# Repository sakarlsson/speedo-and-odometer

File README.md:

# speedo-and-odometer
Arduino based speedometer and odometer

Made to work for my El Camino 1970 with a Holley Terminator X EFI.

The code is now a bit more generally useful.

The odometer is using a Adafruit Monochrome 128x32 I2C OLED graphic
display [ADA931].  It will store the current km reading in the eeprom
(using a rotating scheme to get more than the 100000 writes per cell).

The speedo is using the SwitechX25 lib.
Beware that this lib has a little flaw when it comes to the zero()
function.  It does not use its acceleration mechanism and steps
may stall.    You may need to tweak this in the SwitechX25.cpp 

```#define RESET_STEP_MICROSEC 800
```

## Usage

### Compile

Use the library manger to fetch the used libs. These are needed:

    #include <Adafruit_GFX.h>
    #include <Adafruit_SSD1306.h>

Compile and load the Arduino with the code using the normal Arduino IDE.

I use: 

	arduino-cli compile -b arduino:avr:nano
	arduino-cli upload -p /dev/ttyUSB0  -b arduino:avr:nano:cpu=atmega328old
	
	arduino-cli monitor  -p /dev/ttyUSB0

### Run

Use the Arduino serial console to configure the speedometer.
You need to issue the following commands:

* `set zeromark value`  To configure the position of the zero speed mark.
* `set maxmark value`   To configure the position of the maximum speed mark
* `set maxspeed value`  To configure what speed it is at the max speed mark

To help you figure out the positions you can use

    moveto position

It will move the dial to the poistion - the position is in terms steps of the Switec motor.
When you have found the position of zero, give `set zero <value>`, and the
position will be saved to the internal eeprom.  Proceed with finding the position for
the max speed mark. 

When you have set the above 3 parameters, you can try it out by simulating
a speed:

    speed 120

## General mounting etc

I used the Arduino Nano for a small form factor and milled out a plastic console
out of POM to hold it all together.

For the tachometer I had to CNC mill a new needle as I couldn't reuse the original.

The speedo will get power from the IGN 12+V, but the tachometer will have constant
battery power. As it will not otherwise be able to go to Zero when you turn off the IGN.

The tachometer code will enter Low Power mode when there are no pulses detected, and
did draw about 2-3 mA (after I desoldered the power LED on the Nano).

The Holley Terminator X was programmed to output the Speed on one of the free output pins.

# draw-gauge.py 

Is a small script that works with the Inkscape Simple Scripting extension 

## Useful links:

https://guy.carpenter.id.au/gaugette/2012/01/19/x12-quad-driver-chip/

### To find the X25 driver search for: 

X12.017 AX1201728 AX1201728SG SOP-28

## X27 motor pins 

The X27 168 has built in stops at 0 and max
Pin out: Poke the needle pin at your nose and orient the text X27 168 so you can read it.
         Then pin 1 is to the top left (protruding out on the the other side)
         pin 2 follows counter clock wise, then 3 and 4 which is to the top right.

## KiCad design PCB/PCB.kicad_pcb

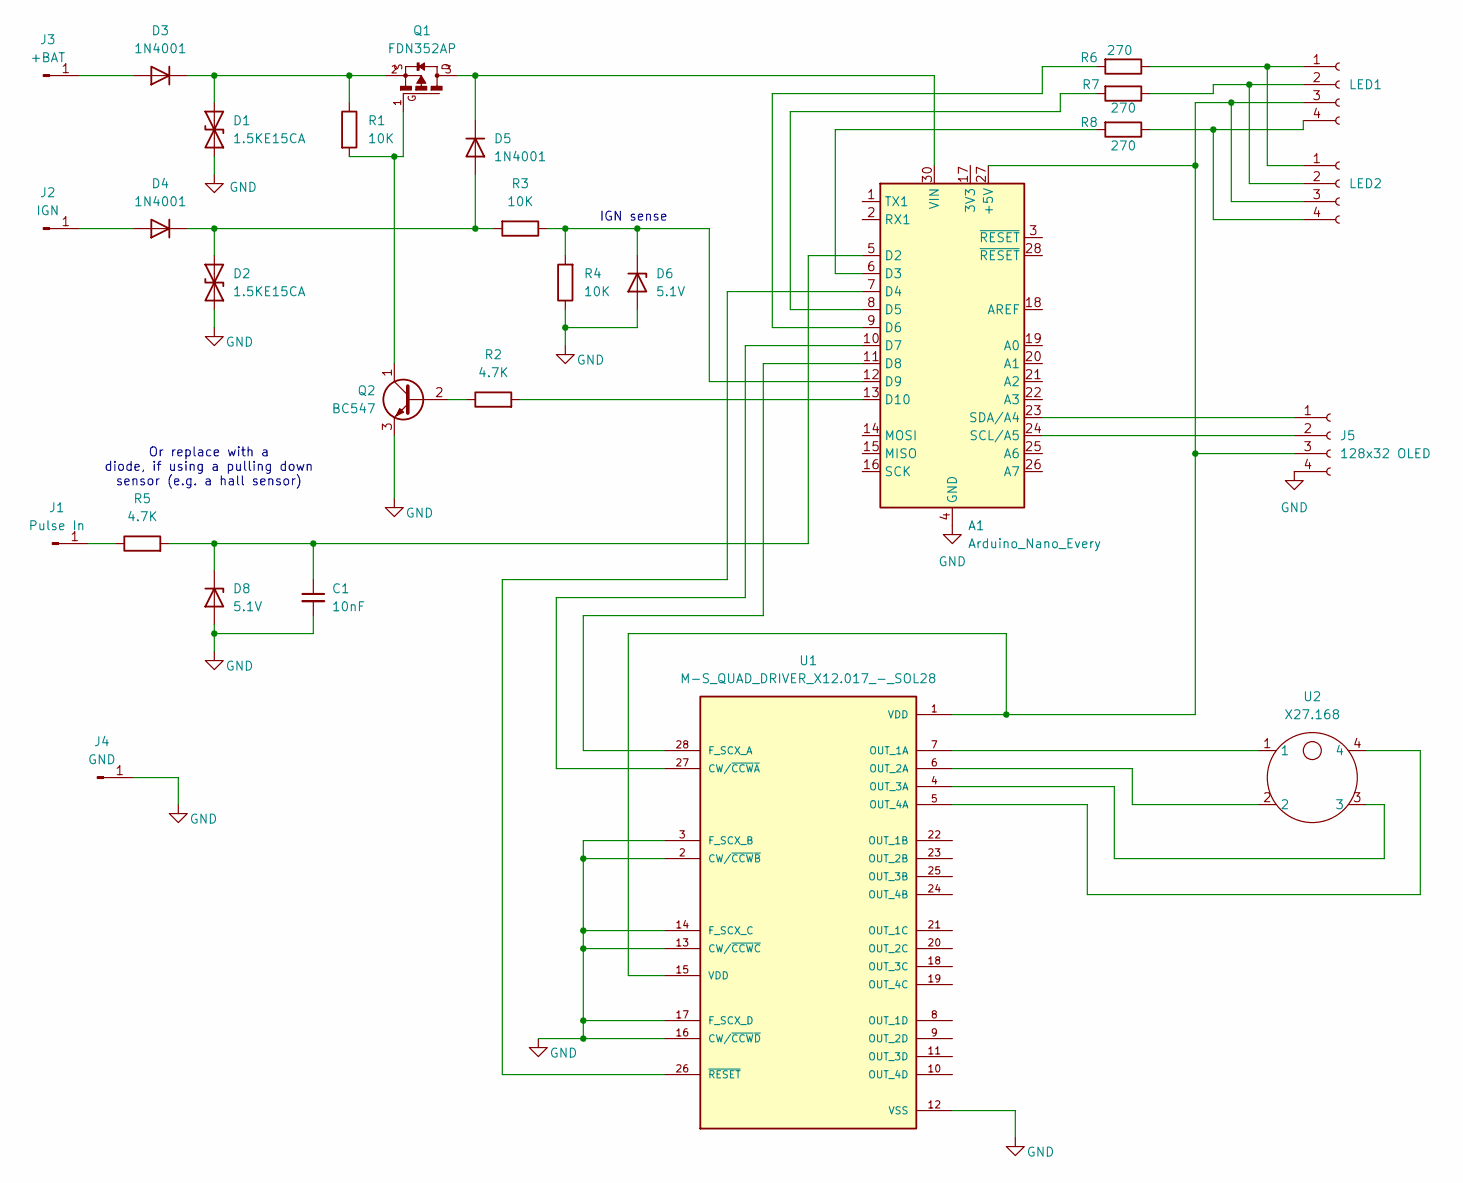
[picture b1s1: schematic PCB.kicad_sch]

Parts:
A1: Arduino_Nano_Every; Arduino_Nano
C1: 10nF; C_Disc_D7.5mm_W4.4mm_P5.00mm
D1, D2: 1.5KE15CA; D_DO-201AE_P5.08mm_Vertical_KathodeUp
D3, D4, D5: 1N4001; D_DO-41_SOD81_P3.81mm_Vertical_KathodeUp
D6, D8: 5.1V; D_DO-35_SOD27_P2.54mm_Vertical_KathodeUp
J1: Pulse In; SolderWire-0.5sqmm_1x01_D0.9mm_OD2.3mm
J2: IGN; SolderWire-0.5sqmm_1x01_D0.9mm_OD2.3mm
J3: +BAT; SolderWire-0.5sqmm_1x01_D0.9mm_OD2.3mm
J4: GND; SolderWire-0.5sqmm_1x01_D0.9mm_OD2.3mm
J5: 128x32 OLED; PinHeader_1x04_P2.54mm_Vertical
LED1: LED1; rgb-led
LED2: LED2; rgb-led
Q1: FDN352AP; SSOT-3
Q2: BC547; TO-92_Inline
R1, R3, R4: 10K; R_Axial_DIN0207_L6.3mm_D2.5mm_P2.54mm_Vertical
R2, R5: 4.7K; R_Axial_DIN0207_L6.3mm_D2.5mm_P2.54mm_Vertical
R6, R7, R8: 270; R_Axial_DIN0207_L6.3mm_D2.5mm_P2.54mm_Vertical
U1: M-S_QUAD_DRIVER_X12.017_-_SOL28; SOIC127P1028X264-28N; PARTREV --
U2: X27.168; x27.168

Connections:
GND: A1.4 (GND), A1.29 (GND), C1.2, D1.1 (A1), D2.1 (A1), D6.2 (A), D8.2 (A), J4.1, J5.4, Q2.3 (E), R4.1, U1.2 (CW/~CCW~B), U1.3 (F_SCX_B), U1.12 (VSS), U1.13 (CW/~CCW~C), U1.14 (F_SCX_C), U1.16 (CW/~CCW~D), U1.17 (F_SCX_D)
unnamed: A1.5 (D2), C1.1, D8.1 (K), R5.2
unnamed: A1.6 (D3), R8.2
unnamed: A1.7 (D4), U1.26 (~RESET)
unnamed: A1.8 (D5), R7.2
unnamed: A1.9 (D6), R6.2
unnamed: A1.10 (D7), U1.27 (CW/~CCW~A)
unnamed: A1.11 (D8), U1.28 (F_SCX_A)
unnamed: A1.12 (D9), D6.1 (K), R3.1, R4.2
unnamed: A1.13 (D10), R2.2
unnamed: A1.24 (SCL/A5), J5.2
unnamed: A1.23 (SDA/A4), J5.1
unnamed: A1.30 (VIN), D5.1 (K), Q1.3
unnamed: D1.2 (A2), D3.1 (K), Q1.2, R1.1
unnamed: D2.2 (A2), D4.1 (K), D5.2 (A), R3.2
unnamed: D3.2 (A), J3.1
unnamed: D4.2 (A), J2.1
unnamed: J1.1, R5.1
unnamed: LED1.1, LED2.1, R6.1
unnamed: LED1.2, LED2.2, R7.1
unnamed: LED1.4, LED2.4, R8.1
unnamed: Q2.2 (B), R2.1
unnamed: Q1.1, Q2.1 (C), R1.2
unnamed: U1.7 (OUT_1A), U2.1
unnamed: U1.6 (OUT_2A), U2.2
unnamed: U1.4 (OUT_3A), U2.3
unnamed: U1.5 (OUT_4A), U2.4
VDD: A1.27 (+5V), J5.3, LED1.3, LED2.3, U1.1 (VDD), U1.15 (VDD)

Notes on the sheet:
IGN sense
Or replace with a diode, if using a pulling down sensor (e.g. a hall sensor)

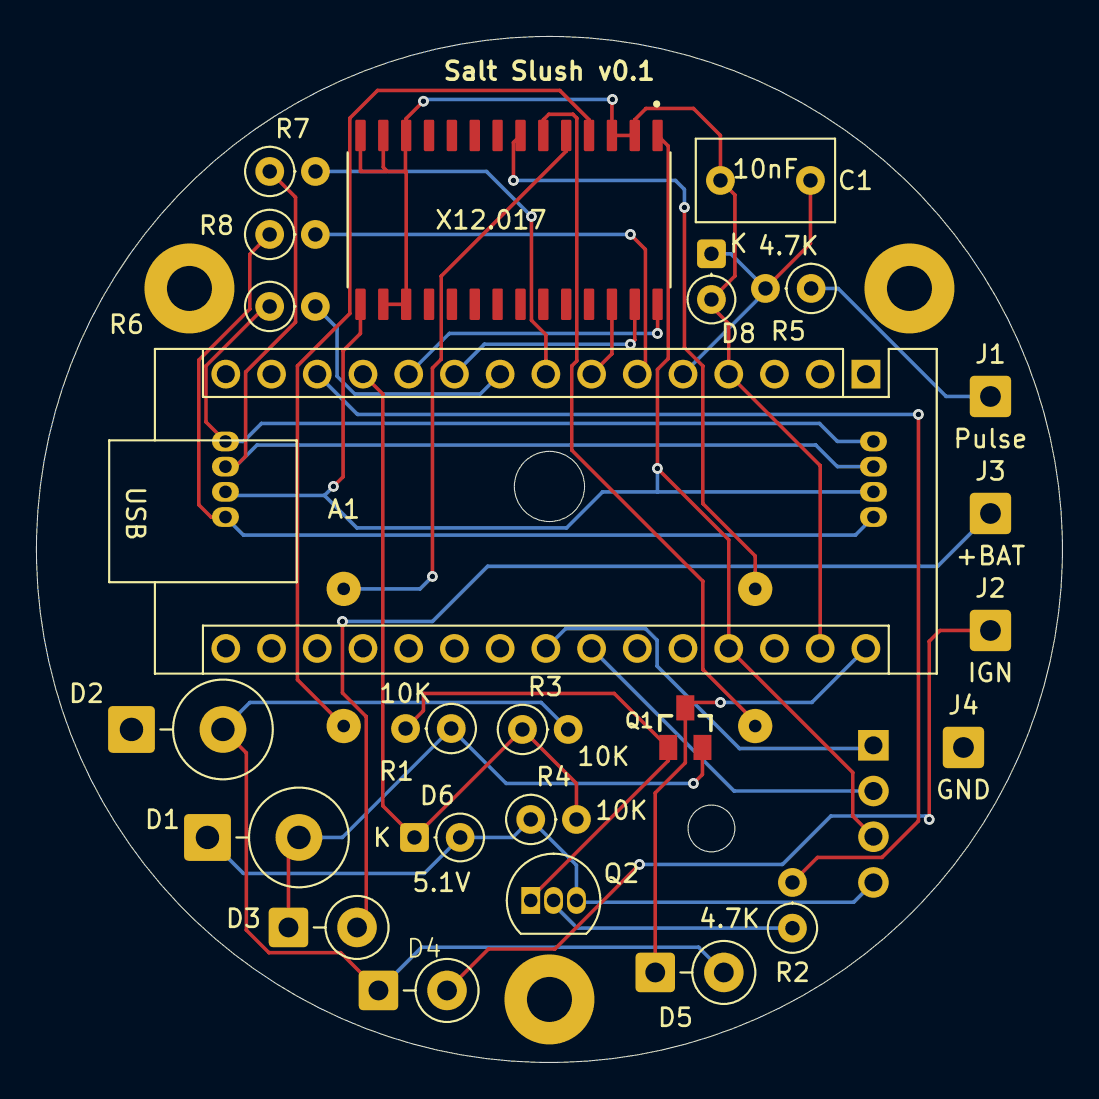
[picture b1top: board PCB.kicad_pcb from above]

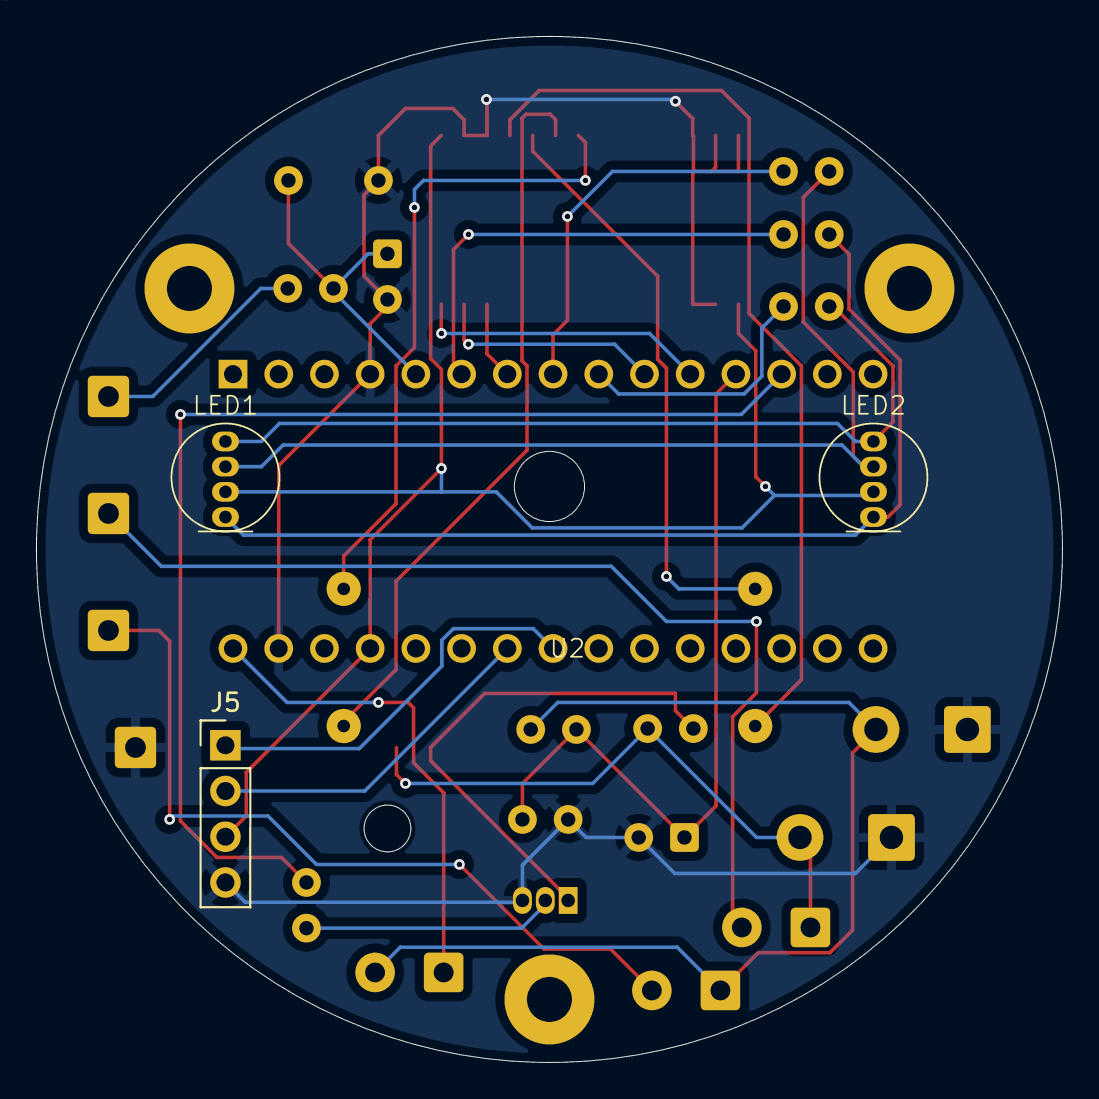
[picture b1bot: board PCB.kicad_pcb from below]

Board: 2 copper layers, 57.0 x 57.0 mm, 28 parts (4 on the bottom side), 28 nets.

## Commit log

2020-02-15 First commit of running code
2020-02-15 Comment on quirk in code
2020-02-15 Add a picture
2020-10-04 Reworked to be more generic.
    The old impl is in my-el-camino branch.
2020-10-04 Update README to document using the new code.
2020-10-04 Improved init message.
2020-10-06 Create LICENSE
2021-02-21 Add a status cmd
2025-10-04 New take using the X12.017 microstep driver
2025-10-09 Fast needs to be <= 200 uS
2026-01-15 Checkpoint after PCB 0.1 was sent to JLPCB
    speedo code remains to convertetd to uS pulse
    logic insteda of a speed based calculation
